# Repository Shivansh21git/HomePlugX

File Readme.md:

# 🔌 HomePlugX

**HomePlugX** is a compact IoT smart plug built around the **ESP32** (or ESP32-S3) platform.  
It enables wireless control, timer, and scheduling of any 230 VAC appliance up to **10 A**, with built-in protection and energy monitoring capability.

---

## ⚙️ Features

- ✅ Wi-Fi control via ESP32 / ESP32-S3
- ⏱️ Timer and scheduling support (App-based)
- ⚡ Energy metering using HLW8012 / HLW8032
- 🔥 Relay control with transistor or MOSFET driver
- 🧰 Built-in surge and over-current protection
- 📱 Android app made using MIT App Inventor
- 💡 Compact, low-power, and safe for home use

---

## 🧩 Hardware Overview

| Section | Component | Function |
|----------|------------|-----------|
| **Power Input** | Fuse + MOV + NTC + X2 Cap | Surge & inrush protection |
| **AC-DC Conversion** | HLK-PM05 | 230 VAC → 5 VDC isolated |
| **Regulator** | SPX3819 / AMS1117 | 5 V → 3.3 V for ESP32 |
| **Relay** | HF46F (10 A) | Switches live line |
| **Driver** | 2N2222 / IRLML2502 | Relay drive transistor / MOSFET |
| **MCU** | ESP32-S3 Mini / ESP32-WROOM | Core controller with Wi-Fi + BT |
| **Energy Meter** | HLW8012 / HLW8032 | Measures current, voltage, power |
| **Enclosure** | Plastic housing | Insulated & compact plug body |

---

## 🔋 Electrical Ratings

| Parameter | Value |
|------------|--------|
| Input Voltage | 230 VAC ±10 % |
| Load Current | Up to 10 A (resistive) |
| Output Power | Up to 2.3 kW |
| Isolation | 3 kV (HLK-PM05) |
| Standby Power | < 1 W |

---

## 🧠 Software Features

- MQTT / HTTP communication  
- Local web control page  
- Countdown timer and real-time clock scheduling  
- OTA firmware update (optional)  
- Energy-usage reporting and overload cut-off  

---

## 🧰 Development Stack

- **Firmware:** Arduino IDE / ESP-IDF  
- **Mobile App:** MIT App Inventor  
- **PCB Design:** KiCad / EasyEDA  
- **Database / Visualization (optional):** InfluxDB + Grafana  
- **Version Control:** Git + GitHub  

---

## 🛠️ Getting Started

### 1. Hardware Setup
1. Assemble HLK-PM05, protection components, relay, and MCU as per schematic.  
2. Flash firmware using USB-to-UART converter.  
3. Power the board **only through isolation** during initial testing.

### 2. Firmware Flash
```bash
git clone https://github.com/yourusername/HomePlugX.git
cd HomePlugX
# open in Arduino IDE or ESP-IDF and upload

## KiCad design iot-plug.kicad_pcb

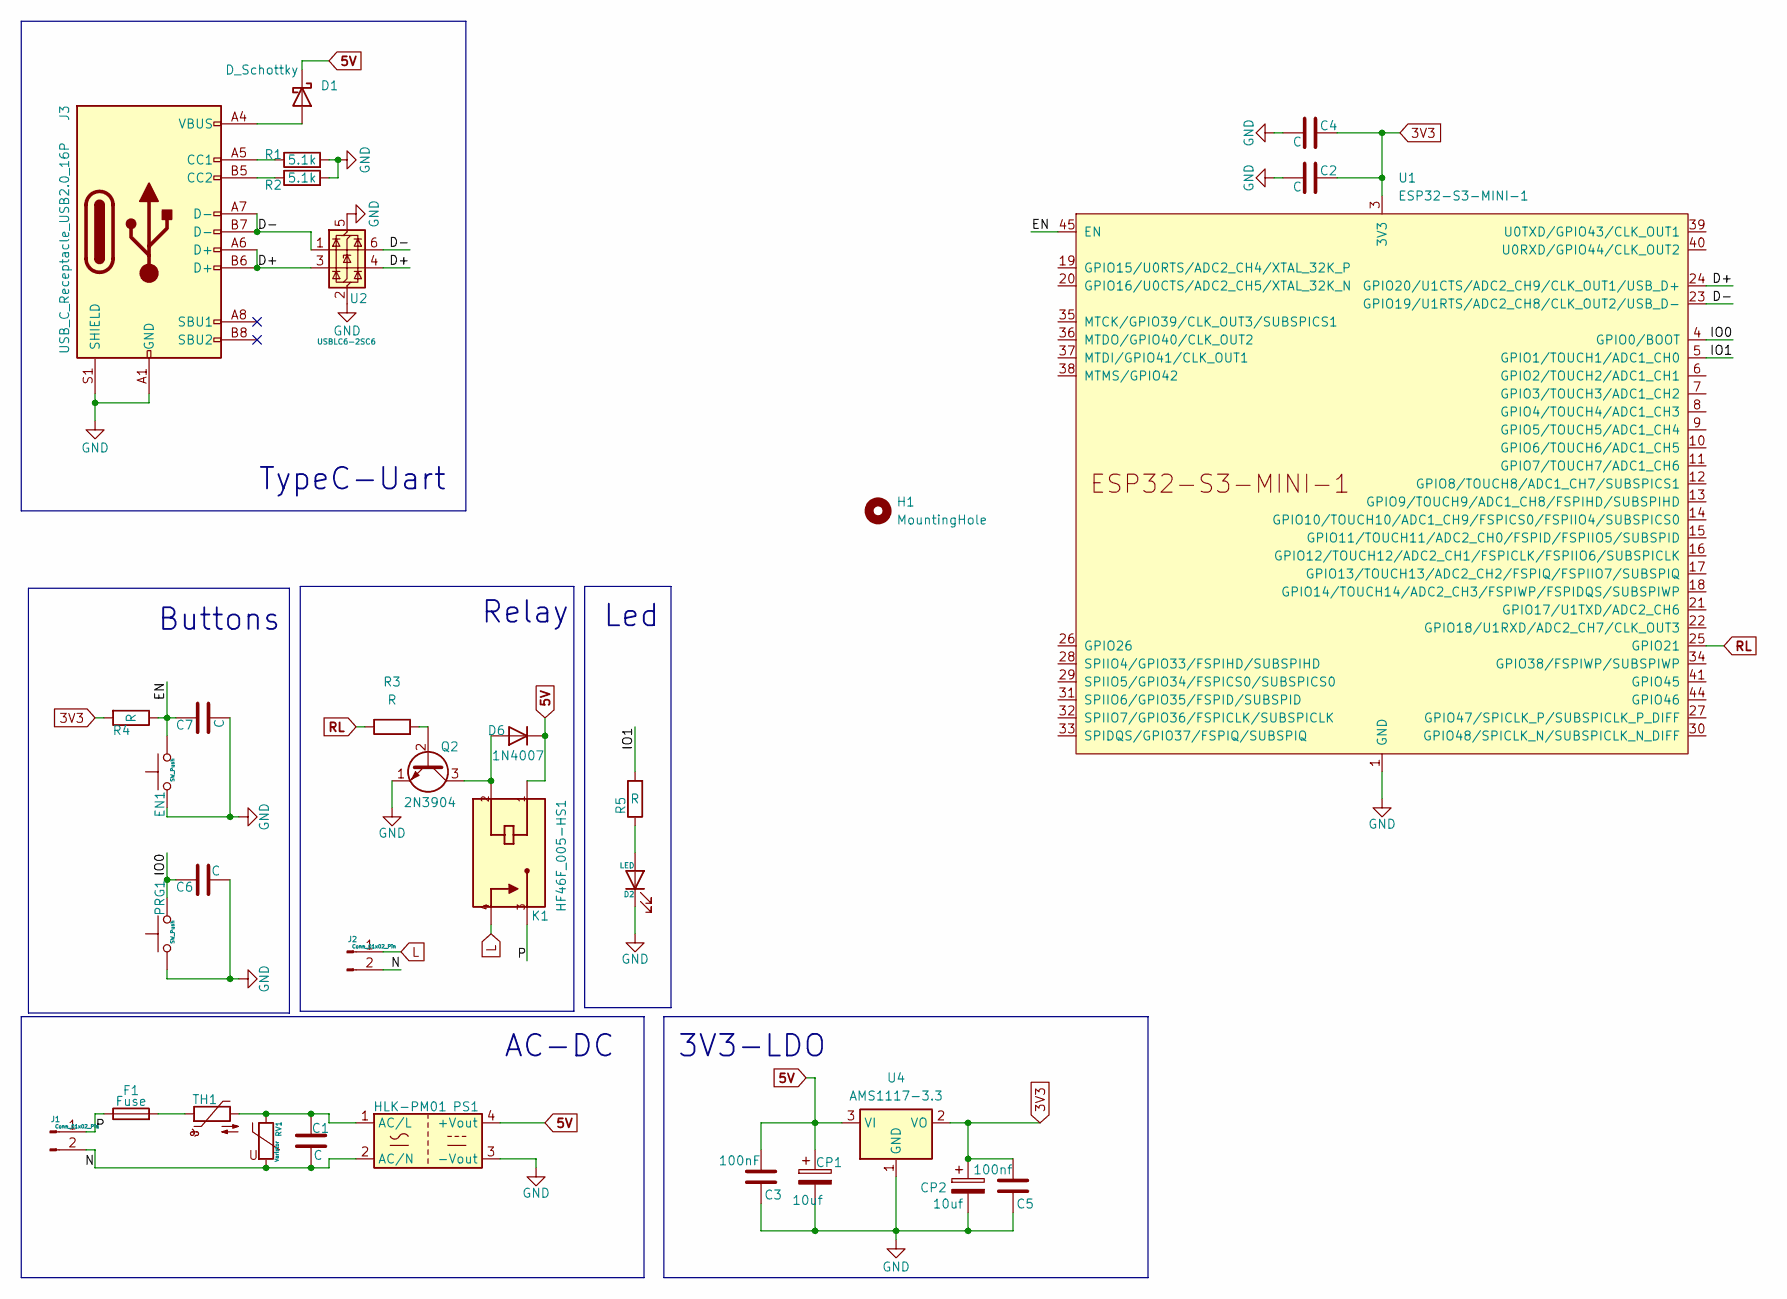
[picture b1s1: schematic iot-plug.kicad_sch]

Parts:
C1: C; C_Rect_L13.5mm_W5.0mm_P10.00mm_FKS3_FKP3_MKS4
C2, C4, C6, C7: C; C_0805_2012Metric
C3: 100nF; C_0805_2012Metric_Pad1.18x1.45mm_HandSolder
C5: 100nf; C_0805_2012Metric_Pad1.18x1.45mm_HandSolder
CP1, CP2: 10uf; C_0805_2012Metric_Pad1.18x1.45mm_HandSolder
D1: D_Schottky; R_0805_2012Metric_Pad1.20x1.40mm_HandSolder
D2: LED; LED_1206_3216Metric
D6: 1N4007; D_SOD-123F
EN1: SW_Push; SW_Push_SPST_NO_Alps_SKRK
F1: Fuse; Fuseholder_Cylinder-5x20mm_Stelvio-Kontek_PTF78_Horizontal_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
H1: MountingHole; MountingHole_3.2mm_M3
J1, J2: Conn_01x02_Pin; SolderWire-1sqmm_1x02_P5.4mm_D1.4mm_OD2.7mm
J3: USB_C_Receptacle_USB2.0_16P; USB_C_Receptacle_GCT_USB4105-xx-A_16P_TopMnt_Horizontal
K1: HF46F_005-HS1; RELAY_HF46F_005-HS1; PARTREV 1.00
PRG1: SW_Push; SW_Push_SPST_NO_Alps_SKRK
PS1: HLK-PM01; Converter_ACDC_Hi-Link_HLK-PMxx
Q2: 2N3904; TO-92_Inline
R1, R2: 5.1k; R_0805_2012Metric_Pad1.20x1.40mm_HandSolder
R3: R; R_Axial_DIN0204_L3.6mm_D1.6mm_P1.90mm_Vertical
R4, R5: R; R_0805_2012Metric
RV1: Varistor; RV_Disc_D12mm_W3.9mm_P7.5mm
TH1: Thermistor_NTC; R_Axial_DIN0204_L3.6mm_D1.6mm_P2.54mm_Vertical
U1: ESP32-S3-MINI-1
U2: USBLC6-2SC6; SOT-23-6
U4: AMS1117-3.3; SOT-223-3_TabPin2

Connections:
3V3: C2.1, C4.1, C5.2, CP2.1, R4.2, U1.3 (3V3), U4.2 (VO)
5V: C3.2, CP1.1, D1.1 (K), D6.1 (K), K1.1, PS1.4 (+Vout), U4.3 (VI)
/D+: J3.A6 (D+), J3.B6 (D+), U1.24 (GPIO20/U1CTS/ADC2_CH9/CLK_OUT1/USB_D+), U2.3 (I/O2), U2.4 (I/O2)
/D-: J3.A7 (D-), J3.B7 (D-), U1.23 (GPIO19/U1RTS/ADC2_CH8/CLK_OUT2/USB_D-), U2.1 (I/O1), U2.6 (I/O1)
/EN: C7.1, EN1.2, R4.1, U1.45 (EN)
/IO0: C6.1, PRG1.2, U1.4 (GPIO0/BOOT)
/IO1: R5.2, U1.5 (GPIO1/TOUCH1/ADC1_CH0)
/N: C1.2, J1.2, J2.2, PS1.2 (AC/N), RV1.2
/P: F1.1, J1.1, K1.3
GND: C2.2, C3.1, C4.2, C5.1, C6.2, C7.2, CP1.2, CP2.2, D2.1 (K), EN1.1, J3.A1 (GND), J3.A12 (GND), J3.B1 (GND), J3.B12 (GND), J3.S1 (SHIELD), PRG1.1, PS1.3 (-Vout), Q2.1 (E), R1.2, R2.2, U1.1 (GND), U1.2 (GND), U1.42 (GND), U1.43 (GND), U1.46 (GND), U1.47 (GND), U1.48 (GND), U1.49 (GND), U1.50 (GND), U1.51 (GND), U1.52 (GND), U1.53 (GND), U1.54 (GND), U1.55 (GND), U1.56 (GND), U1.57 (GND), U1.58 (GND), U1.59 (GND), U1.60 (GND), U1.61 (GND), U1.62 (GND), U1.63 (GND), U1.64 (GND), U1.65 (GND), U2.2 (GND), U2.5 (VBUS), U4.1 (GND)
L: J2.1, K1.4
unnamed: D1.2 (A), J3.A4 (VBUS), J3.A9 (VBUS), J3.B4 (VBUS), J3.B9 (VBUS)
unnamed: D2.2 (A), R5.1
unnamed: D6.2 (A), K1.2, Q2.3 (C)
unnamed: F1.2, TH1.1
unnamed: J3.A5 (CC1), R1.1
unnamed: J3.B5 (CC2), R2.1
unnamed: C1.1, PS1.1 (AC/L), RV1.1, TH1.2
unnamed: Q2.2 (B), R3.2
RL: R3.1, U1.25 (GPIO21)

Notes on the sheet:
3V3-LDO
TypeC-Uart
Relay
Buttons
AC-DC
Led

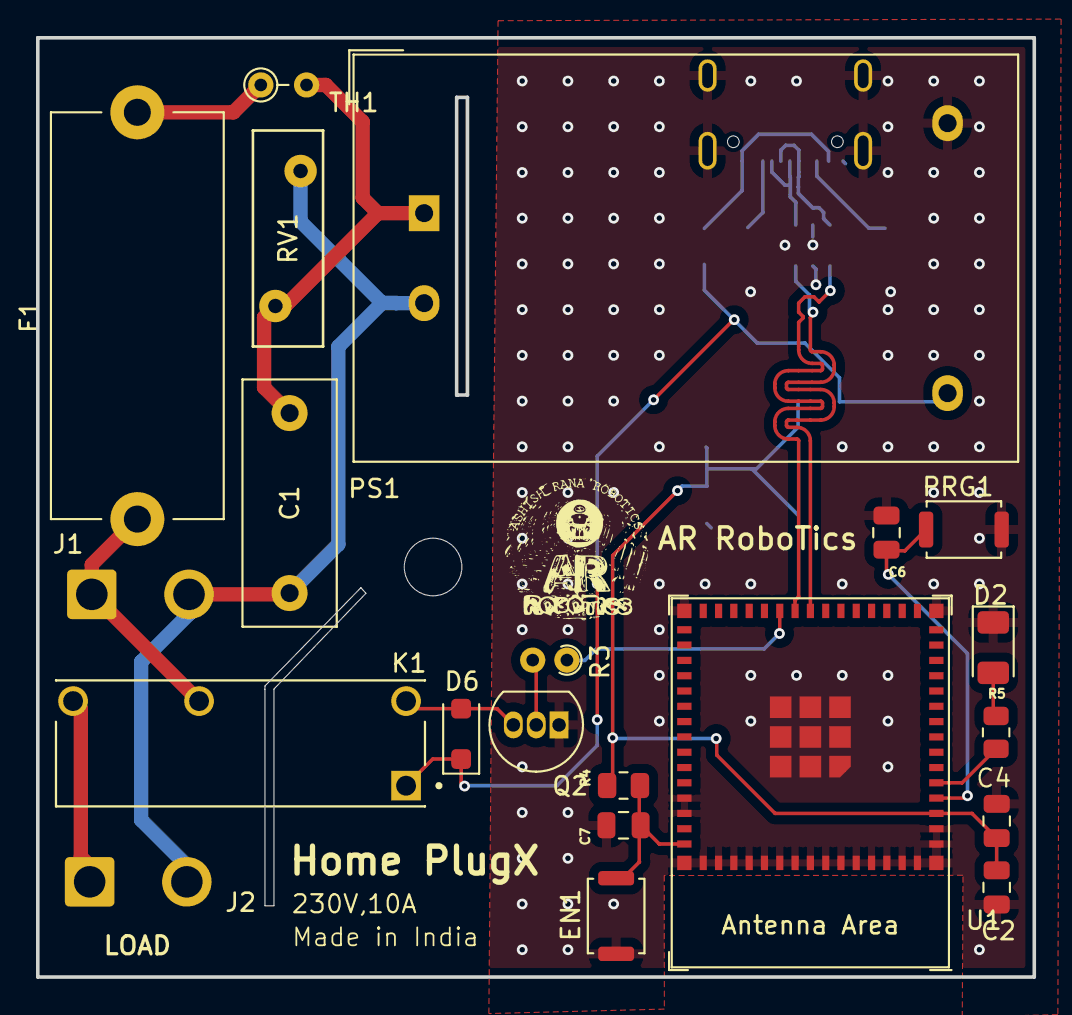
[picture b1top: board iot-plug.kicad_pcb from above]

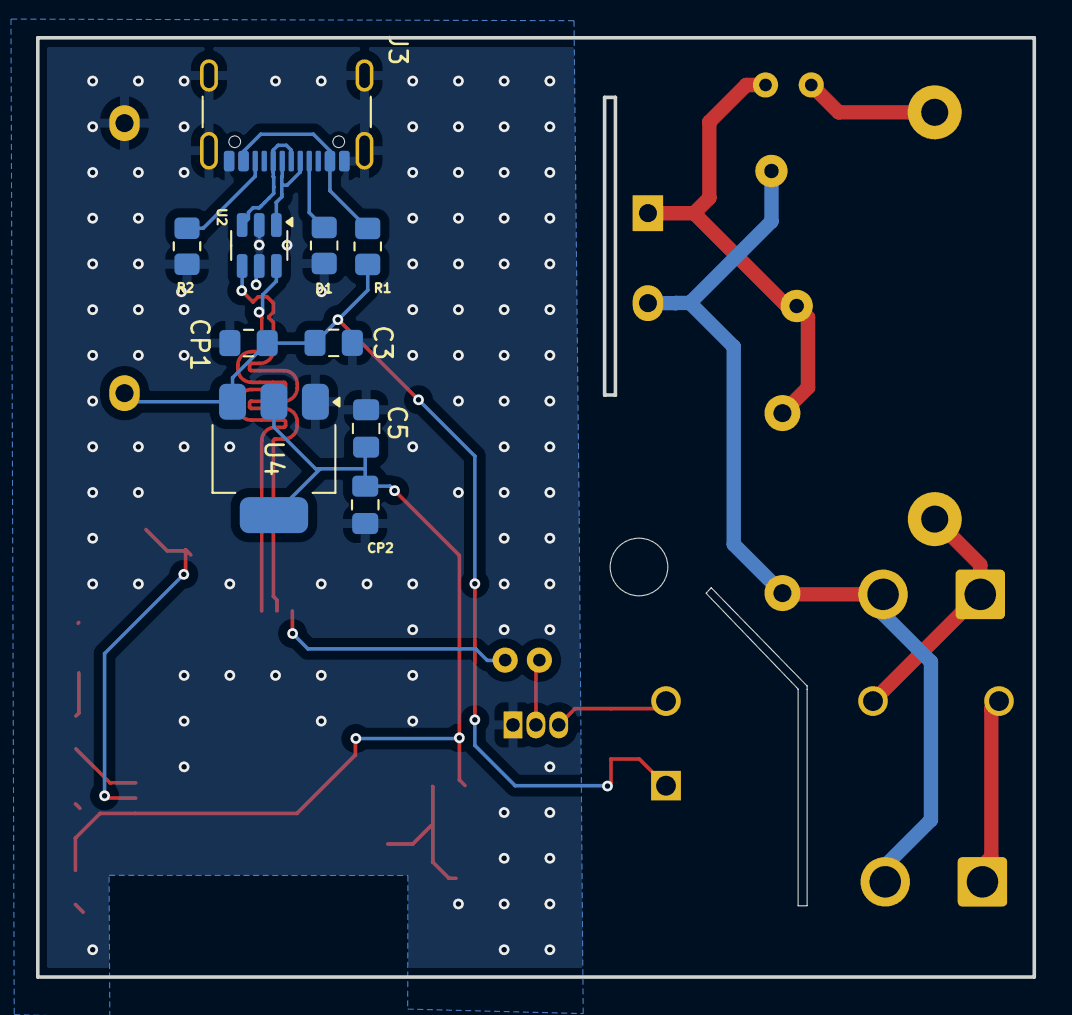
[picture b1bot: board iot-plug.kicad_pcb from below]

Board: 2 copper layers, 55.4 x 52.2 mm, 32 parts (10 on the bottom side), 20 nets.

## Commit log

2025-11-02 initial commit from coolPC
2025-11-02 3d-folder
2025-11-02 from shivpc
2025-11-03 layout updated
2025-11-03 logo added
2025-11-03 updated- from msi
2025-11-05 updated tracks & nets
